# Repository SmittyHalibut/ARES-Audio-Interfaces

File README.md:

# ARES-Audio-Interfaces
My implementation of the SLOECC ARES Headset interface. See http://www.sloecc.org/headsets/ for details.

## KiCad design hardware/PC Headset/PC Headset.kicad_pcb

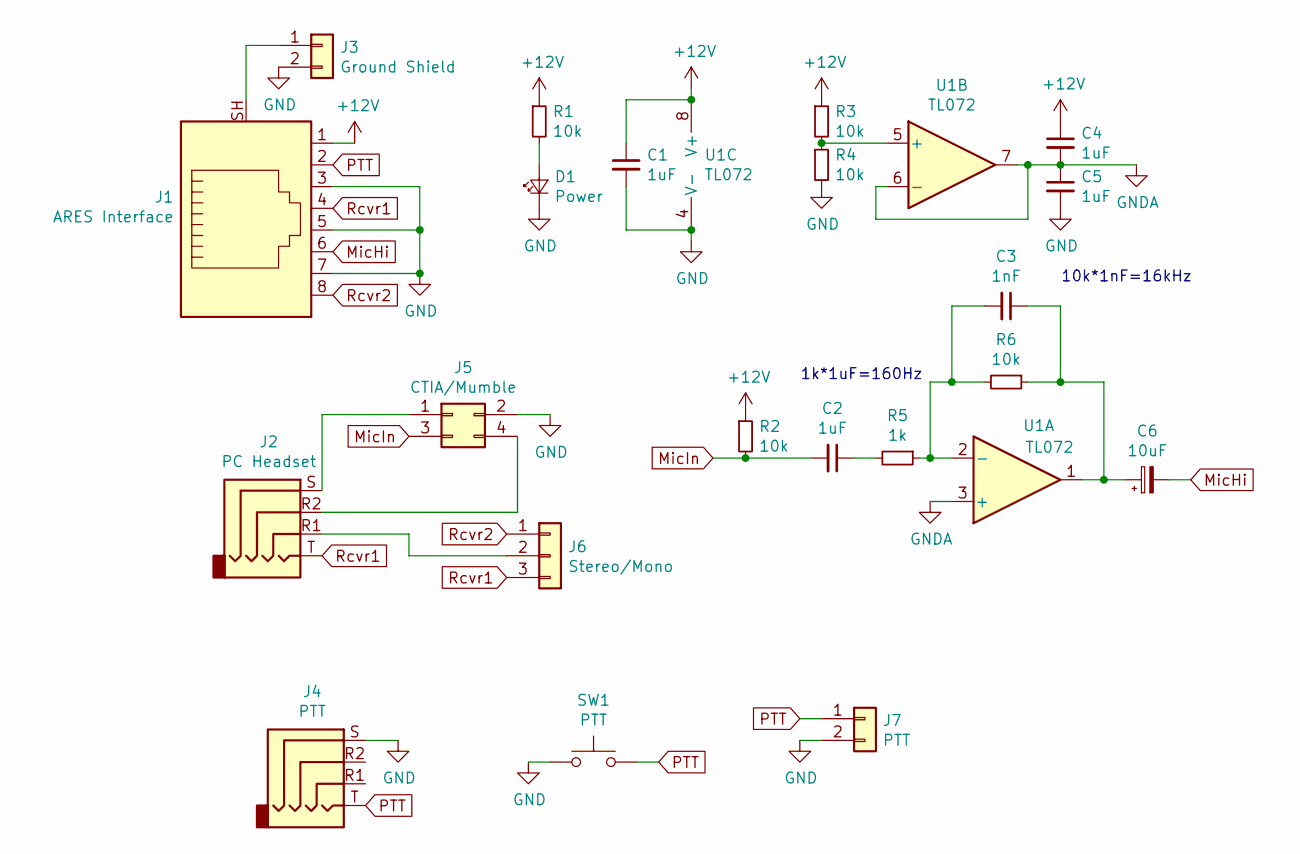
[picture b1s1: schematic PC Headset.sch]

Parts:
C1, C2, C4, C5: 1uF; C_1206_3216Metric_Pad1.42x1.75mm_HandSolder
C3: 1nF; C_1206_3216Metric_Pad1.42x1.75mm_HandSolder
C6: 10uF; CP_Radial_D7.5mm_P2.50mm
D1: Power; LED_D3.0mm
J1: ARES Interface; RJ-45
J2: PC Headset; Conn-3.5mm-TRRS-PJ-320L
J3: Ground Shield; PinHeader_1x02_P2.54mm_Vertical
J4: PTT; Conn-3.5mm-TRRS-PJ-320L
J5: CTIA/Mumble; PinHeader_2x02_P2.54mm_Vertical
J6: Stereo/Mono; PinHeader_1x03_P2.54mm_Vertical
J7: PTT; PinHeader_1x02_P2.54mm_Vertical
R1, R2, R3, R4, R6: 10k; R_1206_3216Metric_Pad1.42x1.75mm_HandSolder
R5: 1k; R_1206_3216Metric_Pad1.42x1.75mm_HandSolder
SW1: PTT; SW_PUSH_6mm_H8mm
U1: TL072; SOIC-8_3.9x4.9mm_P1.27mm

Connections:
+12V: C1.1, C4.1, J1.1, R1.1, R2.1, R3.1, U1.8 (V+)
GND: C1.2, C5.2, D1.1 (K), J1.3, J1.5, J1.7, J3.2, J4.S, J5.2, J7.2, R4.2, SW1.1, U1.4 (V-)
GNDA: C4.2, C5.1, U1.3 (+), U1.6 (-), U1.7
MicHi: C6.2, J1.6
MicIn: C2.2, J5.3, R2.2
unnamed: C2.1, R5.2
unnamed: C3.1, C6.1, R6.1, U1.1
unnamed: C3.2, R5.1, R6.2, U1.2 (-)
unnamed: D1.2 (A), R1.2
unnamed: J1.SH, J3.1
unnamed: J2.R1, J6.2
unnamed: J2.R2, J5.4
unnamed: J2.S, J5.1
unnamed: R3.2, R4.1, U1.5 (+)
PTT: J1.2, J4.T, J7.1, SW1.2
Rcvr1: J1.4, J2.T, J6.3
Rcvr2: J1.8, J6.1

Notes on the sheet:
1k*1uF=160Hz
10k*1nF=16kHz

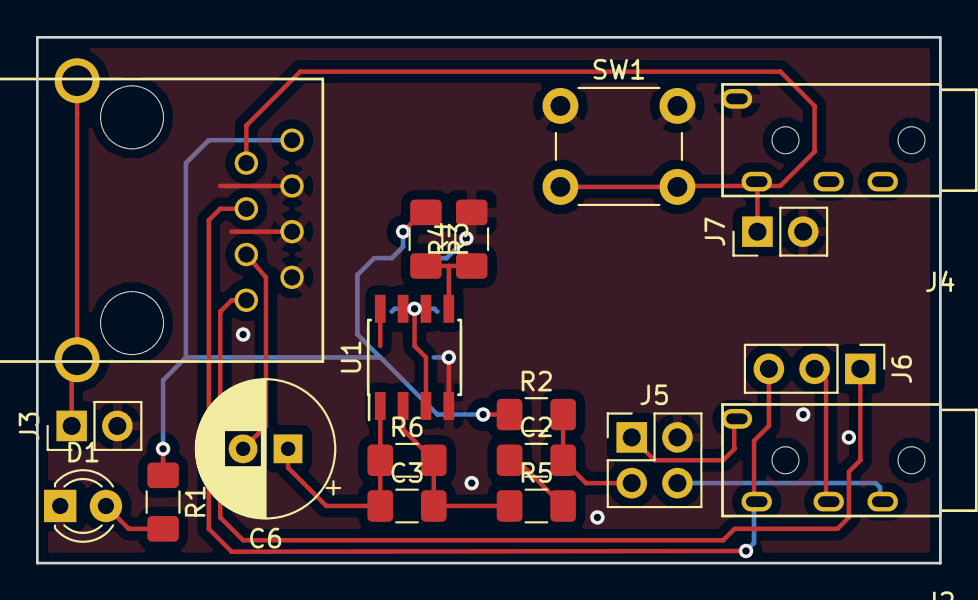
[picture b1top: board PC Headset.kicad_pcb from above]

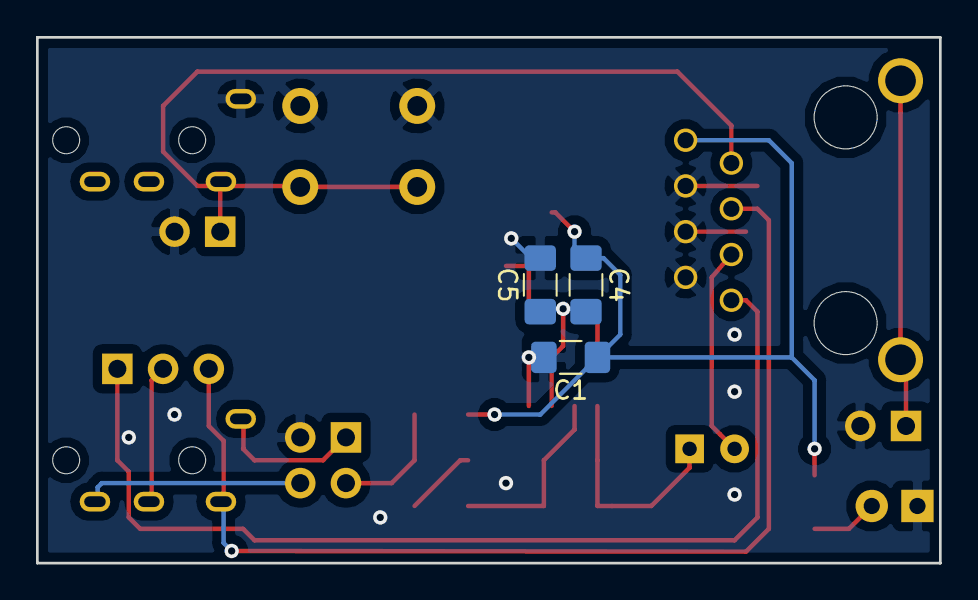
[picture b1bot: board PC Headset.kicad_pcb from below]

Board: 2 copper layers, 50.2 x 29.2 mm, 22 parts (3 on the bottom side), 17 nets.

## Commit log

2020-03-10 PC Headset, 4 pin TRRS, to ARES standard interface.
